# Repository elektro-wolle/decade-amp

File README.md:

# Selectable Decade Amplifier

Due to my - in the highest sensitive ranges - a little bit noisy Rigol DS-1054z scope, I decided to provide a small pre-amplifier for low-voltage measurements (a.k.a. electret microphone signals, shunt-voltages, etc.).
For best performance in the micro-volt range, a dual stage amplifier (both stages provide 10V/1V gain) is built with the [MCP6V27](http://www.microchip.com/wwwproducts/en/MCP6V27). A third and last stage gives the final 10V/1V amplification resulting in a gain of 1000V/1V with a 3db cut-off at ~200 kHz.

For the third stage and the virtual ground a cheaper [MCP6292](http://www.microchip.com/wwwproducts/en/MCP6292) is used.

**The input voltage must not exceed ±1.5V!**

Current consumption should be ~1.6mA, the CR2032 coin-cell should last about 200h. The slide-switch disables the op-amps, if 1V/1V is selected.

Further improvements:
*  TVS-Diodes for clamping input voltage?

## Schematic

### BOM

Ref|QTY|Value|Mouser
---|---|---|---
BT1|1|Keystone 1058|Keystone 1058
C1, C2, C3|3|22pF|885012007002
C4, C5|2|100nF|C0805C104K5RACTU
J1, J2|2|Conn_Coaxial|TE-5-1634503-1
R1, R7, R12|3|1k|RR1220P-102-D
R2, R8, R13|3|6k8|RR1220P-682-D
R3, R9, R14|3|2k2|RR1220P-222-D
R6, R5|2|100k|RR1220P-104-D
R11, R4, R10, R15|4|270R|RC0805JR-07270RL
SW1|1|SS-24E06-TG 5 (P)|SS-24E06-TG 5 (P)
U1|1|MCP6V27-E/SN|MCP6V27-E/SN
U2|1|MCP6292-E/SN|MCP6292-E/SN

## Final device

## Licence 
[Attribution-NonCommercial 4.0 International (CC BY-NC 4.0)](https://creativecommons.org/licenses/by-nc/4.0/) 2018 Wolfgang Jung, Ideas In Logic - Jung & Kesten GbR

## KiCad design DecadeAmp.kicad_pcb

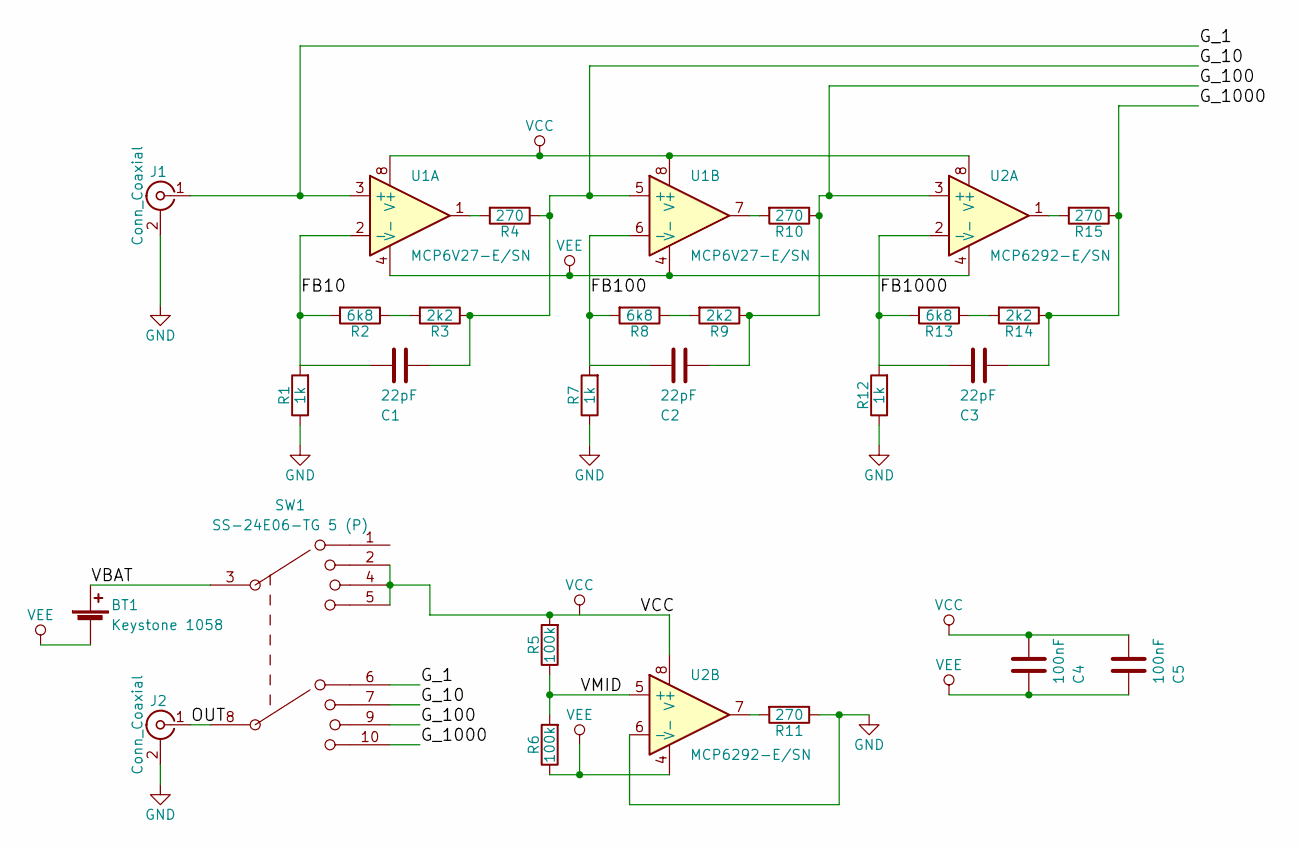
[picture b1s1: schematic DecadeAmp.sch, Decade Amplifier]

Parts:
BT1: Keystone 1058; Keystone_1058_1x2032-CoinCell
C1, C2, C3: 22pF; C_0805_2012Metric
C4, C5: 100nF; C_0805_2012Metric
J1, J2: Conn_Coaxial; BNC_TEConnectivity_1478204_Vertical
R1, R7, R12: 1k; R_0805_2012Metric
R2, R8, R13: 6k8; R_0805_2012Metric
R3, R9, R14: 2k2; R_0805_2012Metric
R4, R10, R11, R15: 270; R_0805_2012Metric
R5, R6: 100k; R_0805_2012Metric
SW1: SS-24E06-TG 5 (P)
U1: MCP6V27-E/SN; SOIC-8_3.9x4.9mm_P1.27mm
U2: MCP6292-E/SN; SOIC-8_3.9x4.9mm_P1.27mm

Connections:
/FB10: C1.2, R1.2, R2.2, U1.2 (-)
/FB100: C2.2, R7.2, R8.2, U1.6 (-)
/FB1000: C3.2, R12.2, R13.2, U2.2 (-)
/G_1: J1.1 (In), SW1.6, U1.3 (+)
/G_10: C1.1, R3.1, R4.1, SW1.7, U1.5 (+)
/G_100: C2.1, R9.1, R10.1, SW1.9, U2.3 (+)
/G_1000: C3.1, R14.1, R15.1, SW1.10
/OUT: J2.1 (In), SW1.8
/VBAT: BT1.1 (+), SW1.3
/VMID: R5.1, R6.2, U2.5 (+)
GND: J1.2 (Ext), J2.2 (Ext), R1.1, R7.1, R11.1, R12.1, U2.6 (-)
unnamed: R2.1, R3.2
unnamed: R4.2, U1.1
unnamed: R8.1, R9.2
unnamed: R10.2, U1.7
unnamed: R11.2, U2.7
unnamed: R13.1, R14.2
unnamed: R15.2, U2.1
VCC: C4.1, C5.1, R5.2, SW1.2, SW1.4, SW1.5, U1.8 (V+), U2.8 (V+)
VEE: BT1.2 (-), C4.2, C5.2, R6.1, U1.4 (V-), U2.4 (V-)

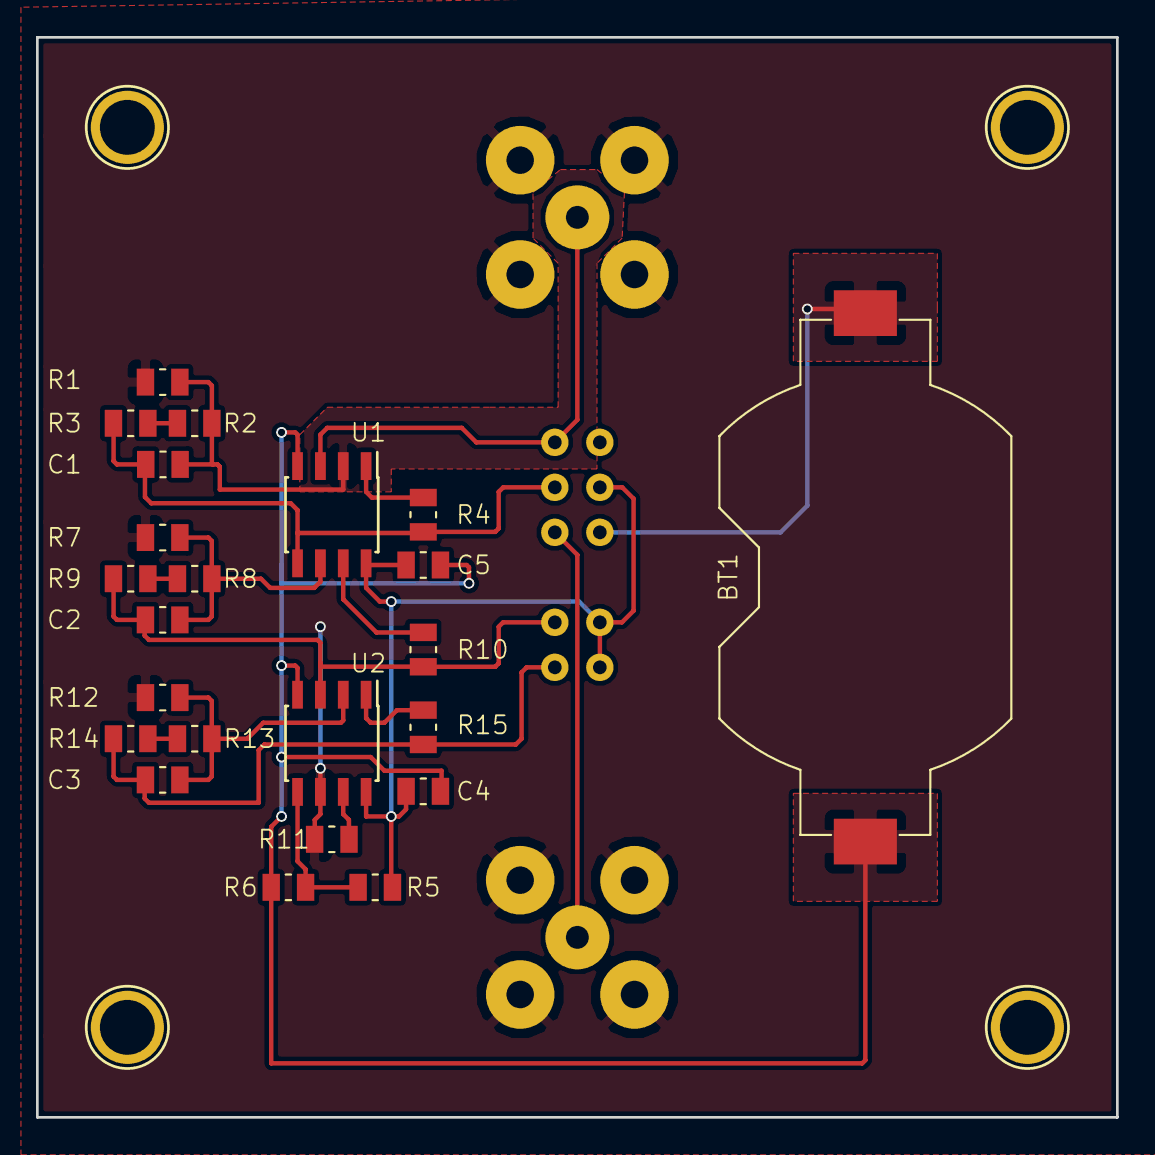
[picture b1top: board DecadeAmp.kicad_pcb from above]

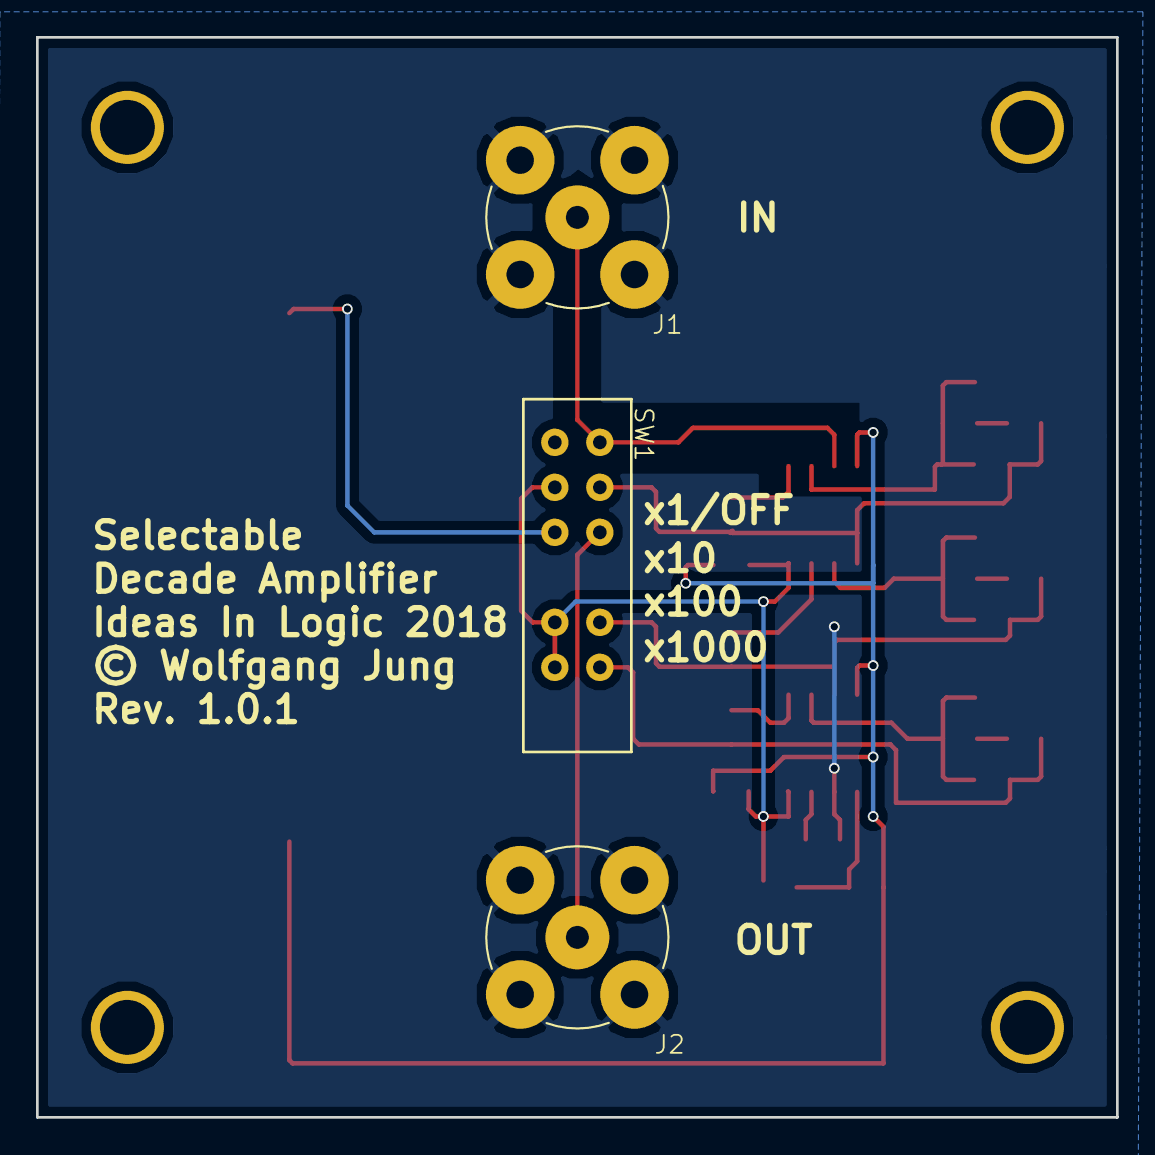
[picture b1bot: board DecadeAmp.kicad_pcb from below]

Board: 2 copper layers, 60.0 x 60.0 mm, 26 parts (3 on the bottom side), 20 nets.

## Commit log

2018-01-15 Initial version decade amp
2018-01-16 Correct Op-Amp MCP6292-E/SN
2018-01-16 Better fill
2018-01-16 BOM added
2018-01-26 moved to new packages
2018-02-03 Better silkscreen, vendor-IDs of all components
2018-02-03 README and documentation added
2018-02-06 Typo corrected

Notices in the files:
DecadeAmp.kicad_pcb:
© Wolfgang Jung
DecadeAmp.sch:
© 2018 Wolfgang Jung
